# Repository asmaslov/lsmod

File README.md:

# Light & Sound Module for The Toy Lightsaber

This is a completely open hardware and software project.  
The main idea is to create a tiny electronic module that imitates light and sound effects of a Lightsaber.  
Lightsaber is a well-know Jedi weapon from the fantasy universe of [Star Wars](https://en.wikipedia.org/wiki/Star_Wars), created by George Lucas.

## Overview

Module is hidden inside the hilt of a toy Lightsaber. It has a battery power and works autonomously.  
  
Module is waiting in a standby mode for a signal from the button. When the button is pressed the module turns on all the LEDs on the strip one by one and plays a corresponding sound effect. Then in idle mode the module plays repetitively a humming sound and continuously reads accelerometer data. When a movement is detected the module selects hit or swing sound effect according to calculated intensity. In case of the contact with any conductive object the module repetitively plays a clash sound until the contact is lost. Pressing a button again activates the shutdown cycle, module turns off all the LEDs in reverse order and plays a corresponding sound effect.  
The color of the LEDs and all the sound effects are configurable and are kept in the non-volatile memory. Configuration is done by the desktop application which connects to the module via a maintenance interface.

## Repository Contents

* **avr-board/** - Schematics and board design project
* **avr-firmware/** - Firmware sources for the module board
* **doc/** - General project documentation files
* **package/** - Everything you need for manufacturing and assembly of a specific module version (gerbers, binary firmware files, schematics and board design files)
* **service/** - A desktop application sources
* **tracks/** - A collection of selected sound effects for every module operation mode

## Subsystems
Current version (v1.0) is in fact an experimental one. It's purpose was to research and study all the aspects of making such a module. It is based on ATmega168 microcontroller. The firmware barely fits to the microcontroller memory, so there is a obvious reason to think about radical platform change. But for now it is what it is. Honestly speaking, I did it with what was at hand at that moment.

### Accelerometer
Current version have two options for an accelerometer.  
The analogue one is based on ADXL330 and occupies several channels of the internal ADC of the microcontroller. It's fast and simple to use, but a little noisy. Possibly due to poor accuracy of internal ADC.  
The digital one is based on MMA7455L and needs the I2C interface. It's more complex to use and requires more logic in the firmware. But it's accuracy seems better, despite some asynchrony in the data transmission.  
Apparently, only one accelerometer type should be chosen for future design.

### Contact Sensor
This is most controversial idea in the project. Contact sensor is in fact a touch sensor based on AT42QT1011. The solution is working somehow, but obviously needs further development. Touch sensor pin is soldered to the metal base of the LEDs strip. Sometimes it activates from static electricity, and sometimes it doesn't work at all even with direct finger touch. More research work required here.

### Light Control
Multicolored RGB strip is based on series of WS2811 LEDs. It has a custom one-bit protocol and designed to support a serial connection of multiple LEDs. Surprisingly, I did't have any problems with this LEDs and a strip of nearly 20 pieces never had false behavior of any single LED. However, they require a lot of power. The small internal battery died very quickly. So, I had to use larger and rechargeable one. There is a problem with power insufficiency in the schematics, check out problems section below.  
There are some predefined colors according to the movie story. Choose wisely, young apprentice!  

### Sound Playback
Sound effects are played with a speaker and an amplifier TDA7267. The sound itself is generated with PDM logic. Samples are stored in the external flash AT45DB321B. Flash does not have any file system, so samples are stored in raw data format. Address and length of every track (sequence of samples) is stored in the EEPROM memory of the microcontroller.  
The sound quality is rather good. I used some generic 28 mm speaker and even heard some bass notes. Sounds are well guessed and quite similar to the original ones from the movies.

## Board and Schematics
Go to the `avr_board` folder. Here you can find schematics and board design files made with [Eagle CAD 7.6.0](http://eagle.autodesk.com/eagle/software-versions/2) program.  
The schematics required only two-layered board. So it's possible to make an assembly without any special equipment. Only a simple solderer and a lot of patience. I did not used resistors or capacitors smaller than 0805.  
When the first version was tested, I revealed a lot of problems in the schematics, all are listed in the problems section below.  
However, the module works and gave a lot of fun when shown to close friends. They didn't expected a real Jedi to visit them one evening! As they say, every true Jedi must make his own lightsaber.

## Software

### Firmware
To build the firmware you need avr-gcc toolchain installed. I used [WinAVR](https://winavr.sourceforge.net/) when building in Windows.  
Go to the `avr_firmware` folder and simply run `make` in shell. The binary is `avr_firmware/build/lsmod.hex` file.  
To load the firmware you need an ISP programmer and an [avrdude](https://www.nongnu.org/avrdude/) utility. I used [AVR Dragon](https://www.digikey.com/en/products/detail/microchip-technology/ATAVRDRAGON/1124251), but I'm sure any ISP programmer would fit. You may need to change *DUDE_PRG* variable in the Makefile to make it work. Run `make test` to check programmer is fine.  
Then run `make prog` to load the firmware.  
You may also need to set fuses. Run `make fuse` to do it.

### Desktop Application
The application is written in Python and is based on PyQt5 framework. It's working fine with [Python 3.8.10](https://www.python.org/downloads/release/python-3810/) distribution.  
Obviously you need the Qt5 framework. I used [Qt 5.9.2](https://download.qt.io/archive/qt/5.9/5.9.2/).  
Go to the `service` folder and run `make setup` to install some additional Python packages first.  
Then run `make` to create files necessary for Python script.  
If you would like to make a single executable to run without any external libraries run `make distro` and check it out inside `service/dist` folder.  

## Module assembly
The only version available for now is and experimental one (v1.0). Files are in the `package` folder.  
However, if you would like to make your own assembly, you are welcome to use gerber files to make the board.  
To view them you can use [gerbview](https://www.gerbview.com/) utility.  
Bill of materials file is also included.  
Moreover, inside the `package` folder there is a prebuilt firmware. The EEPROM data file is only for reference. You still have to load sound files manually.  
They are in the `tracks` folder as well.

## Problems and Wishes
Since it's completely enthusiastic project, I really don't know when I'm going to continue working on it. However I'll leave it here in case I still find some time.  
And let the force be with you. And couple of spare batteries, you're gonna need them!

### Software
* Adjust brightness due to battery charge level - should slightly extend working time;
* Generate some specific malfunction error sound if the battery is low (don't turn on the lightsaber the usual way);
* Measure supply voltage at cold power up (in case RS-232 or USB is connected) - disable normal startup;
* Make light enhancement effects when hit;
* Voltage meter is very unstable - need some filter.

### Design
* Make bottom cover with a speaker like in an old phone (round contacts, no wires);
* Two batteries? Li-Pol accumulator? Separate power line for the LEDs strip? Eats a lot;
* Handle length up to 300 mm;
* Fastening the profile with LEDs strip on some strong adapter brackets - it breaks after couple of real hits;
* Diffuser? A translucent mirror shell? Diodes should not be visible;
* Touch! Foil? Winding the diffuser with wire? Metallic paint?
* LEDs strip IP65 (filled with silicone)?
* Volume knob;
* Battery holders - 2 x 3 AAA? Combined with a speaker? Plug-in block;
* Motion sensors - on the edge of the board (at the maximum distance from the hand);

### Schematics
* Separate 7805 or other 1.5 IC for the strip;
* Connector for programmer WB-6;
* Combined connector "power + speaker";
* Combined connector "strip + touch + buttons + regulator";
* 3.3 V Zener diode for ADC;
* Divide the circuit by elements (in BOM too) into two versions of the motion sensor (analogue, digital);
* Connector for RS-232 (USB in the future) - 5V power supply! And bring it to the side under a separate cutout in the case;
* Remove all solderpads - they are useless;
* Analog touch sensitivity adjust;
* Low frequency amplifier with LM386 volume control - and the brightness control at the same time.

## Licenses and Intellectual Property Rights
Unless otherwise noted, code is licensed under the MIT license (check out LICENSE file).  
Schematics and design is licensed under the CERN-OHL-P license (check out LICENSE file inside `avr_board` folder).  
STAR WARS and LIGHTSABER are trademarks of Lucasfilm Entertainment Company Ltd.

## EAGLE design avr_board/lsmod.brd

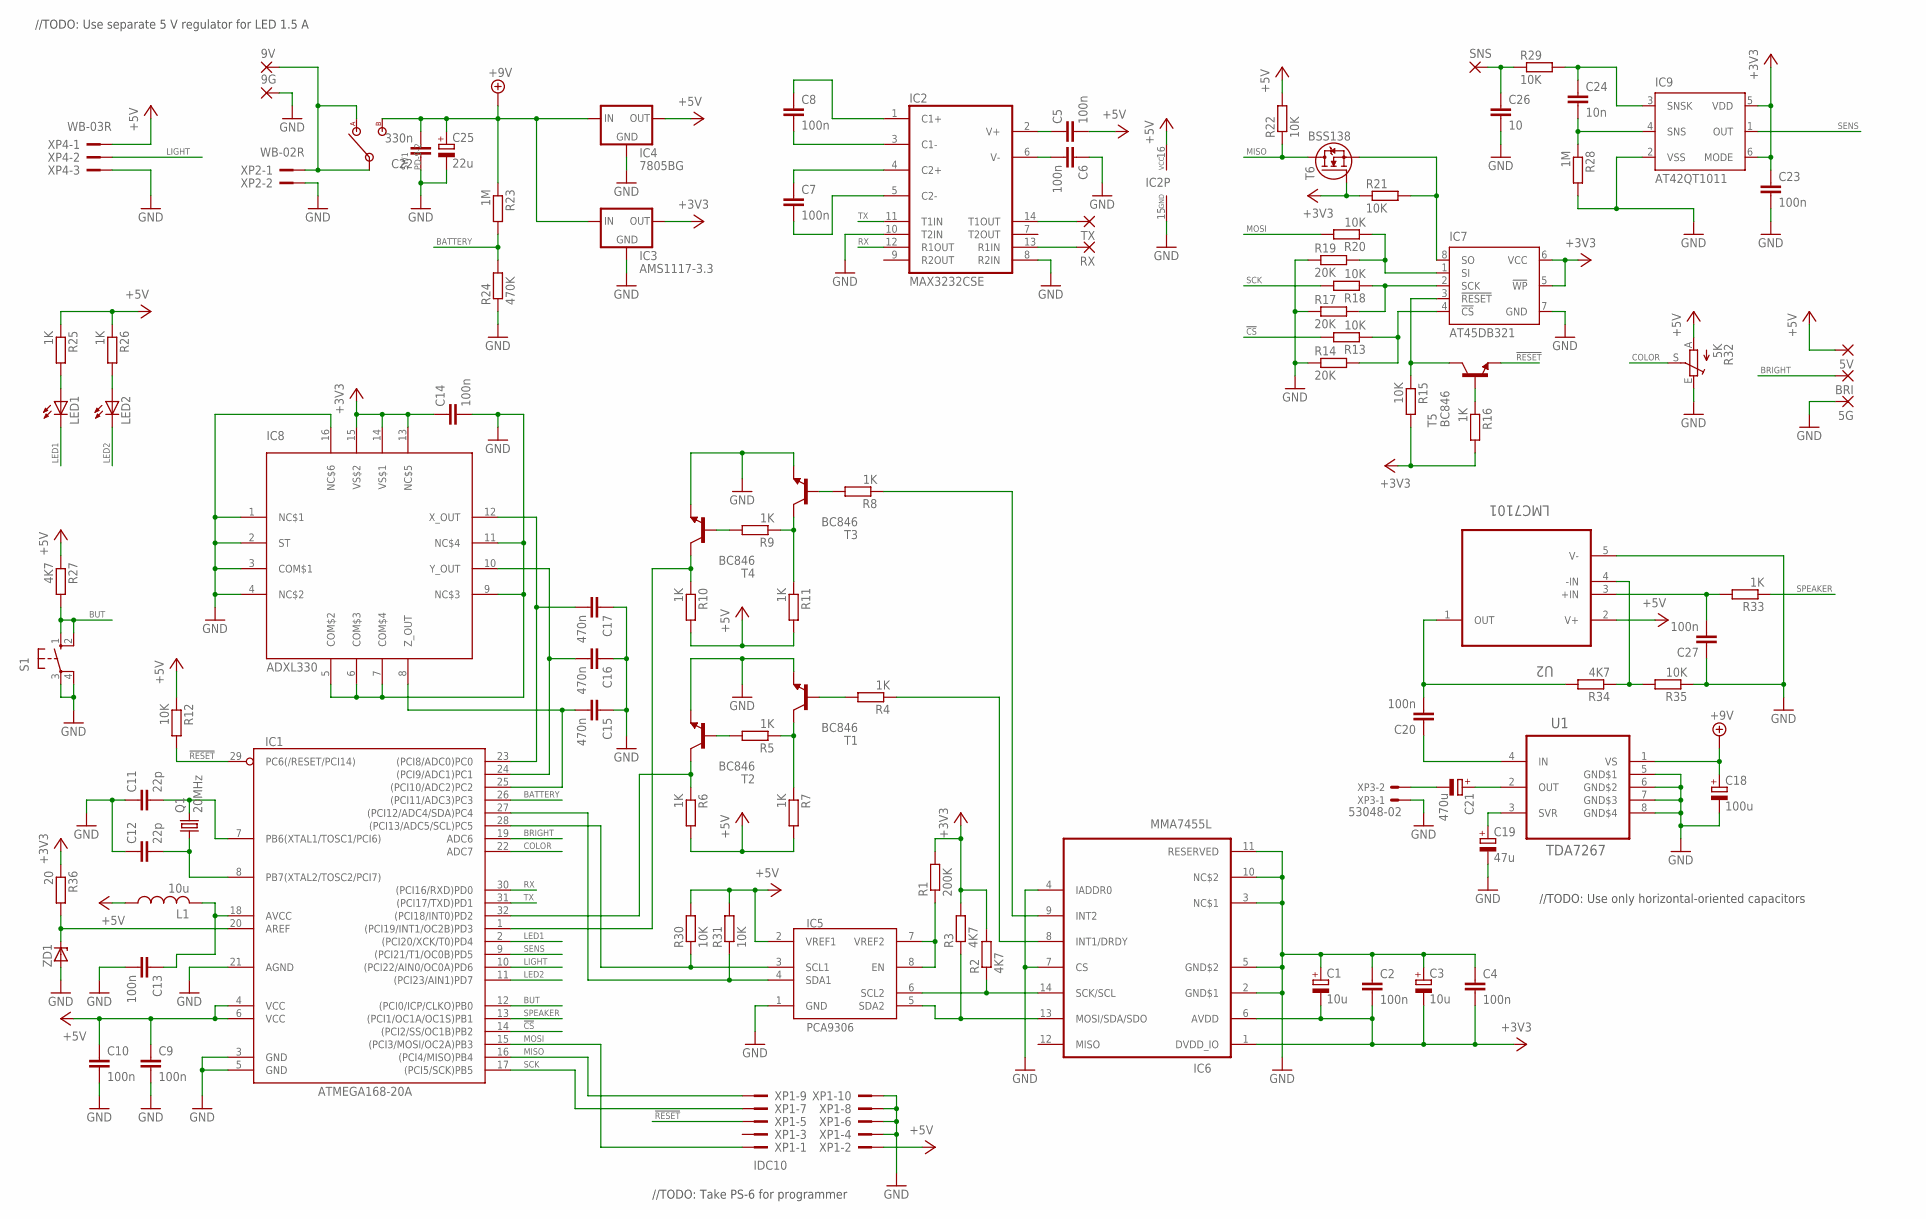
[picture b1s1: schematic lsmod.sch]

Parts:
5G, 5V, 9G, 9V: 2,54/1,0
BRI: 2,54/1,0
C1, C3: 10u; SMC_A
C2, C4, C5, C6, C7, C8, C9, C10, C13, C14, C20, C23, C27: 100n; C0805
C11, C12: 22p; C0805
C15, C16, C17: 470n; C0805
C18: 100u; E2-5
C19: 47u; E2-5
C21: 470u; E3,5-8
C22: 330n; C0805
C24: 10n; C0805
C25: 22u; E2-5
C26: 10; C0805
IC1: ATMEGA168-20A; TQFP32-08
IC2: MAX3232CSE; SO16
IC3: AMS1117-3.3; SOT223
IC4: 7805BG; DPACK
IC5: PCA9306; SM8
IC6: MMA7455L; LGA14
IC7: AT45DB321; SO08
IC8: ADXL330; LFCSP16
IC9: AT42QT1011; SOT23-6
L1: 10u; L2012C
LED1, LED2: LED-SMD
Q1: 20MHz; HC49/S
R1: 200K; R0805
R2, R3, R27, R34: 4K7; R0805
R4, R5, R6, R7, R8, R9, R10, R11, R16, R25, R26, R33: 1K; R0805
R12, R13, R15, R18, R20, R21, R22, R29, R30, R31, R35: 10K; R0805
R14, R17, R19: 20K; R0805
R23: 1M; 0207/10
R24: 470K; 0207/10
R28: 1M; R0805
R32: 5K; B25P
R36: 20; R0805
RX: 2,54/1,0
S1: WS7770S
SNS: 2,54/1,0
SW1: PD-9-2
T1, T2, T3, T4, T5: BC846; SOT23
T6: BSS138; SOT23
TX: 2,54/1,0
U1: TDA7267; DIP8
U2: LMC7101; SOT23-5
XP1: IDC10; BH-10
XP2: WB-02R
XP3: 53048-02
XP4: WB-03R
ZD1: ZD-A1-C3; SOT23

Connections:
!CS: IC1.14 ((PCI2/SS/OC1B)PB2), R13.2
!RESET: IC1.29 (PC6(/RESET/PCI14)), R12.2, T5.2 (E), XP1.5
+3V3: C1.-, C2.2, C3.-, C4.2, C14.1, C23.1, IC3.2 (OUT), IC3.4 (OUT), IC6.1 (DVDD_IO), IC6.6 (AVDD), IC7.5 (!WP), IC7.6 (VCC), IC8.13 (NC$5), IC8.14 (VS$1), IC8.15 (VS$2), IC9.5 (VDD), IC9.6 (MODE), R1.2, R2.2, R3.2, R15.2, R16.2, R21.1, R36.1, T6.1 (G)
+5V: 5V.1, C5.2, C9.1, C10.1, IC1.4 (VCC), IC1.6 (VCC), IC2.16 (VCC), IC4.3 (OUT), IC5.2 (VREF1), L1.1, R6.2, R7.2, R10.2, R11.2, R12.1, R22.2, R25.1, R26.1, R27.1, R30.2, R31.2, R32.A, U2.2 (V+), XP1.2, XP4.1
+9V: C18.+, C22.2, C25.+, IC3.3 (IN), IC4.1 (IN), R23.1, SW1.3 (B), U1.1 (VS)
BATTERY: IC1.26 ((PCI11/ADC3)PC3), R23.2, R24.2
BRIGHT: BRI.1, IC1.19 (ADC6)
BUT: IC1.12 ((PCI0/ICP/CLKO)PB0), R27.2, S1.1 (S), S1.2 (S1)
COLOR: IC1.22 (ADC7), R32.S
GND: 5G.1, 9G.1, C1.+, C2.1, C3.+, C4.1, C6.1, C9.2, C10.2, C11.1, C12.1, C13.2, C14.2, C15.1, C16.1, C17.1, C18.-, C19.-, C22.1, C23.2, C25.-, C26.2, C27.1, IC1.3 (GND), IC1.5 (GND), IC1.21 (AGND), IC2.8 (R2IN), IC2.10 (T2IN), IC2.15 (GND), IC3.1 (GND), IC4.4 (GND), IC5.1 (GND), IC6.2 (GND$1), IC6.3 (NC$1), IC6.4 (IADDR0), IC6.5 (GND$2), IC6.7 (CS), IC6.10 (NC$2), IC6.11 (RESERVED), IC7.7 (GND), IC8.1 (NC$1), IC8.2 (ST), IC8.3 (COM$1), IC8.4 (NC$2), IC8.5 (COM$2), IC8.6 (COM$3), IC8.7 (COM$4), IC8.9 (NC$3), IC8.11 (NC$4), IC8.16 (NC$6), IC9.2 (VSS), R14.1, R17.1, R19.1, R24.1, R28.2, R32.E, R35.1, S1.3, S1.4 (P1), T1.2 (E), T2.2 (E), T3.2 (E), T4.2 (E), U1.5 (GND$1), U1.6 (GND$2), U1.7 (GND$3), U1.8 (GND$4), U2.5 (V-), XP1.4, XP1.6, XP1.8, XP1.10, XP2.2, XP3.1, XP4.3, ZD1.1 (A)
LED1: IC1.2 ((PCI20/XCK/T0)PD4), LED1.C
LED2: IC1.11 ((PCI23/AIN1)PD7), LED2.C
LIGHT: IC1.10 ((PCI22/AIN0/OC0A)PD6), XP4.2
MISO: IC1.16 ((PCI4/MISO)PB4), R22.1, T6.3 (D), XP1.9
MOSI: IC1.15 ((PCI3/MOSI/OC2A)PB3), R20.2, XP1.1
unnamed: IC5.7 (VREF2), IC5.8 (EN), R1.1
unnamed: IC6.9 (INT2), R8.1
unnamed: IC5.5 (SDA2), IC6.13 (MOSI/SDA/SDO), R3.1
unnamed: IC1.32 ((PCI18/INT0)PD2), R6.1, T2.3 (C)
unnamed: R8.2, T3.1 (B)
unnamed: C5.1, IC2.2 (V+)
unnamed: IC5.6 (SCL2), IC6.14 (SCK/SCL), R2.1
unnamed: IC6.8 (INT1/DRDY), R4.1
unnamed: IC1.28 ((PCI13/ADC5/SCL)PC5), IC5.3 (SCL1), R30.1
unnamed: IC1.27 ((PCI12/ADC4/SDA)PC4), IC5.4 (SDA1), R31.1
unnamed: R4.2, T1.1 (B)
unnamed: R9.2, T4.1 (B)
unnamed: R5.1, R7.1, T1.3 (C)
unnamed: R5.2, T2.1 (B)
unnamed: IC1.1 ((PCI19/INT1/OC2B)PD3), R10.1, T4.3 (C)
unnamed: R9.1, R11.1, T3.3 (C)
unnamed: C6.2, IC2.6 (V-)
unnamed: IC2.14 (T1OUT), TX.1
unnamed: C7.2, IC2.5 (C2-)
unnamed: C7.1, IC2.4 (C2+)
unnamed: C8.2, IC2.3 (C1-)
unnamed: C8.1, IC2.1 (C1+)
unnamed: IC2.13 (R1IN), RX.1
unnamed: C13.1, IC1.18 (AVCC), L1.2
unnamed: C11.2, IC1.7 (PB6(XTAL1/TOSC1/PCI6)), Q1.2
unnamed: C12.2, IC1.8 (PB7(XTAL2/TOSC2/PCI7)), Q1.1
unnamed: IC7.4 (!CS), R13.1, R14.2
unnamed: IC7.3 (!RESET), R15.1, T5.3 (C)
unnamed: R16.1, T5.1 (B)
unnamed: IC7.1 (SI), R19.2, R20.1
unnamed: C15.2, IC1.25 ((PCI10/ADC2)PC2), IC8.8 (Z_OUT)
unnamed: IC7.8 (SO), R21.2, T6.2 (S)
unnamed: IC7.2 (SCK), R17.2, R18.1
unnamed: C17.2, IC1.23 ((PCI8/ADC0)PC0), IC8.12 (X_OUT)
unnamed: C16.2, IC1.24 ((PCI9/ADC1)PC1), IC8.10 (Y_OUT)
unnamed: 9V.1, SW1.1 (A), SW1.2 (IN), XP2.1
unnamed: C19.+, U1.3 (SVR)
unnamed: C20.1, U1.4 (IN)
unnamed: C21.+, U1.2 (OUT)
unnamed: C21.-, XP3.2
unnamed: LED1.A, R25.2
unnamed: LED2.A, R26.2
unnamed: C24.2, IC9.4 (SNS), R28.1
unnamed: C24.1, IC9.3 (SNSK), R29.2
unnamed: C26.1, R29.1, SNS.1
unnamed: C20.2, R34.2, U2.1 (OUT)
unnamed: C27.2, R33.2, U2.3 (+IN)
unnamed: R34.1, R35.2, U2.4 (-IN)
unnamed: IC1.20 (AREF), R36.2, ZD1.3 (C)
RX: IC1.30 ((PCI16/RXD)PD0), IC2.12 (R1OUT)
SCK: IC1.17 ((PCI5/SCK)PB5), R18.2, XP1.7
SENS: IC1.9 ((PCI21/T1/OC0B)PD5), IC9.1 (OUT)
SPEAKER: IC1.13 ((PCI1/OC1A/OC1S)PB1), R33.1
TX: IC1.31 ((PCI17/TXD)PD1), IC2.11 (T1IN)

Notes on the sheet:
//TODO: Use separate 5 V regulator for LED 1.5 A
//TODO: Take PS-6 for programmer
//TODO: Use only horizontal-oriented capacitors

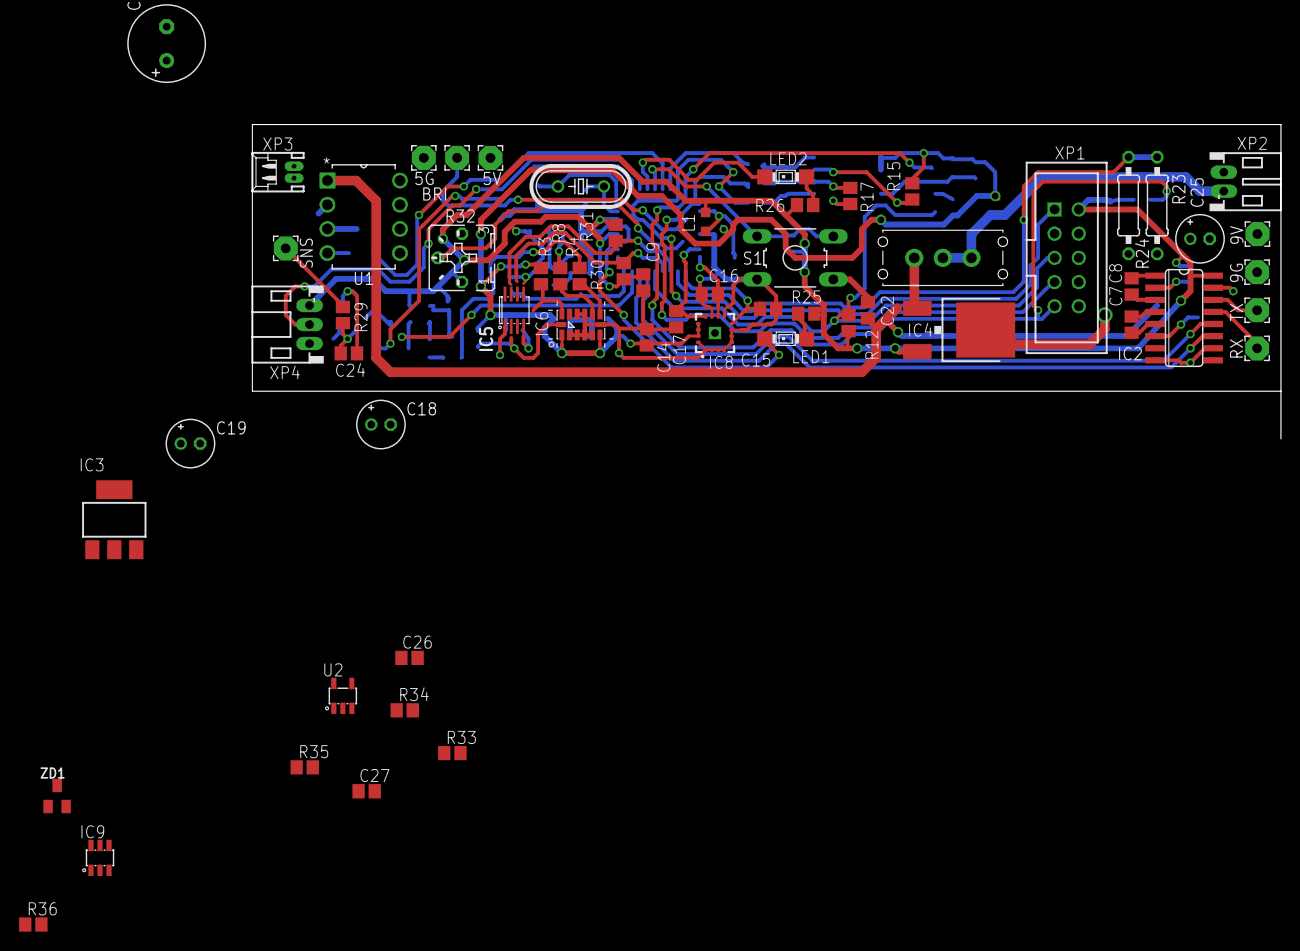
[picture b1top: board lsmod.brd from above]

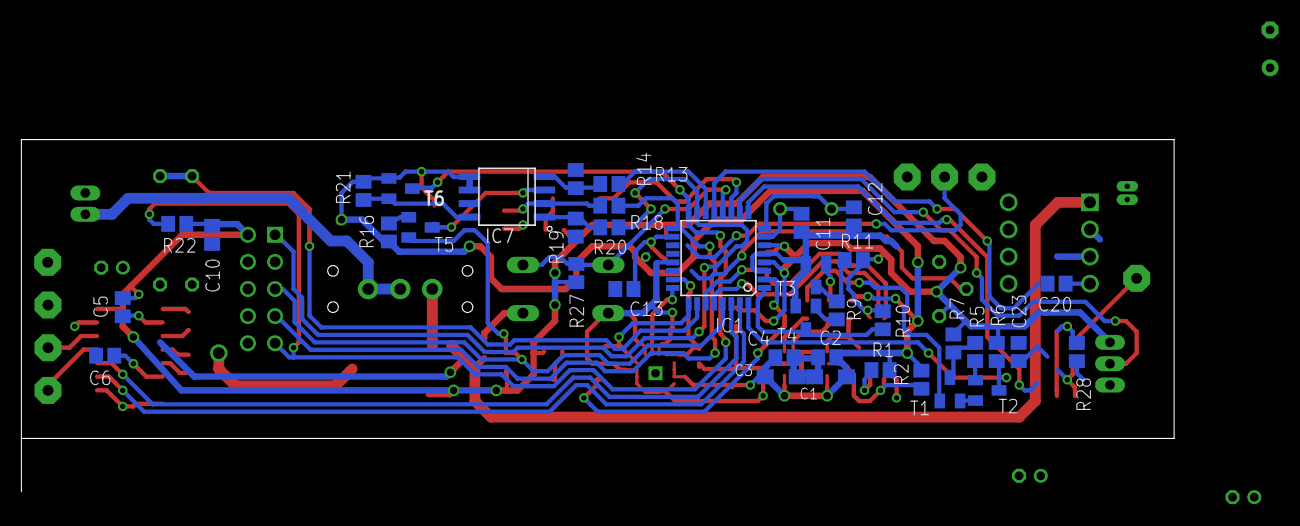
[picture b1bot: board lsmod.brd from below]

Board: 2 copper layers, 108.0 x 28.0 mm, 99 parts (38 on the bottom side), 69 nets.

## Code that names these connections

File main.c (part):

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
void initBoard(void)
{
  PORTB = (1 << PB0);
  DDRB = 0x00;
  PORTC = 0x00;
  DDRC = 0x00;
  PORTD = (1 << PD4) | (1 << PD7);
  DDRD = (1 << DDD4) | (1 << DDD7);
}

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{
  if (on == 0)
  {
    PORTD |= (1 << PD4);
  }
  else
  {
    PORTD &= ~(1 << PD4);
  }
}

void led1Toggle(void)
{
  led1(PORTD & (1 << PD4));
}

void led2(bool on)
{
  if (on == 0)
  {
    PORTD |= (1 << PD7);
  }
  else
  {
    PORTD &= ~(1 << PD7);
  }
}

void led2Toggle(void)
{
  led2(PORTD & (1 << PD7));
}

void commandHandler(void* args)
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
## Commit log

2016-11-15 General debug
2016-11-15 Dataflash alive
2016-11-15 Debug fix
2016-11-15 I2c debug
2016-11-16 Serial communication alive
2016-11-16 Analog mems alive
2016-11-17 Memory savings
2016-11-17 Analog mems by timer
2016-11-17 More savings
2016-11-17 Mems digital filter
2016-11-17 Mems sense adjustments
2016-11-17 Gui template
2016-11-17 Sound file open
2016-11-17 Common improvements
2016-11-17 Sound core template
2016-11-18 Load emulation draft
2016-11-18 Crc fixed
2016-11-18 Dataflash rework draft
2016-11-19 Loaded some in polling mode
2016-11-20 Loading with indexes
2016-11-20 Sound alive
2016-11-20 Sound debug
2016-11-21 Continious play draft
2016-11-22 Interrupt fix
2016-11-22 Major fix
2016-11-22 Sound improved
2016-11-23 Test removed
2016-11-23 Data reply removed
2016-11-23 Output inverse
2016-11-24 Several files load
2016-11-24 Motion play
2016-11-24 File progress bar
2016-11-24 Startup motion filter
2016-11-24 Startup filter fix
2016-11-24 Possible improvement
2016-11-24 Sound freeze fix
2016-11-24 Noise removed
2016-11-26 Bitwidth sample fix
2016-11-27 Basic functional complete
2016-11-27 Play and motion response
2016-11-27 Last track play fix
2016-11-28 Sound logic draft
2016-11-28 Sound logic fix
2016-11-30 Ledrgb draft
2016-11-30 Smooth light effects draft
2016-11-30 Ledrgb mini fix
2016-11-30 Beautify
2016-12-05 Ledrgb alive
2016-12-05 Led freeze fix
2016-12-06 Color picker
2016-12-06 Color load draft
2016-12-06 Colors adjusted
2016-12-17 Limits adjustment
2016-12-17 Sensor delay
2016-12-17 Natural colors preview
2016-12-18 Voltage measure and auto brightness
2020-03-02 Repository transformation
2020-03-11 Cleanup
2023-04-06 Project updated
2023-04-08 License updated
2023-04-08 Update Makefile
